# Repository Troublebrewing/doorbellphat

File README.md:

# doorbellphat
AC-DC psu bonnet/phat for pi zero. To be used with doorbell 12-24VAC.

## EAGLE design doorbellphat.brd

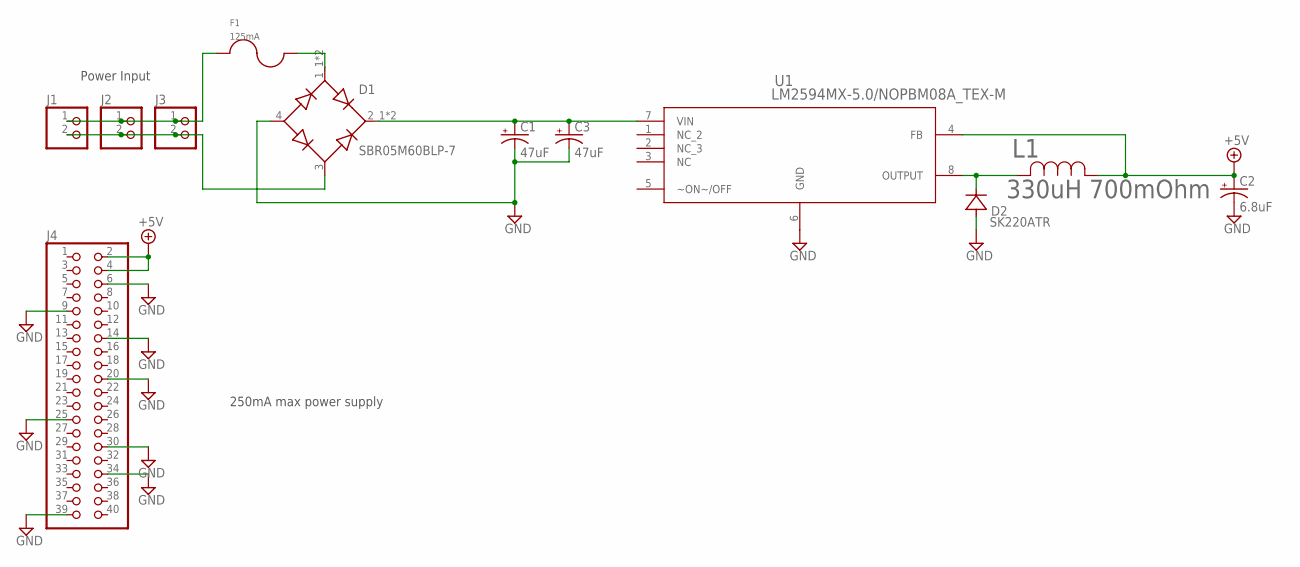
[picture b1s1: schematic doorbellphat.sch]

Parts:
C1, C3: 47uF; CAPPM7343X310N; MFR_PART_NO TAJD476M035RNJV
C2: 6.8uF; 2312; MFR_PART_NO 293D685X9035C2TE3
D1: SBR05M60BLP-7; RECTIFIER_SBR05M60BLP-7
D2: SK220ATR; SMA
F1: 125mA; 0603
J1, J2, J3: PINHD-1X2; 1X02
J4: PINHD-2X20; 2X20
L1: 330uH 700mOhm; IND_BOURNS_SRU1038; MFR_PART_NO SRU1038-331Y
U1: LM2594MX-5.0/NOPBM08A_TEX-M; M08A_TEX-M

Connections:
+5V: C2.A (+), J4.2, J4.4, L1.1, U1.4 (FB)
GND: C1.C (-), C2.C (-), C3.C (-), D1.4 (-), D2.A, J4.6, J4.9, J4.14, J4.20, J4.25, J4.30, J4.34, J4.39, U1.6 (GND)
unnamed: D1.3 (AC2), J1.2, J2.2, J3.2
unnamed: F1.1 (2), J1.1, J2.1, J3.1
unnamed: D2.C, L1.2, U1.8 (OUTPUT)
unnamed: D1.1_1 (AC1), D1.1_2 (AC1), F1.2 (1)
unnamed: C1.A (+), C3.A (+), D1.2_1 (+), D1.2_2 (+), U1.7 (VIN)

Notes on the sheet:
250mA max power supply
Power Input

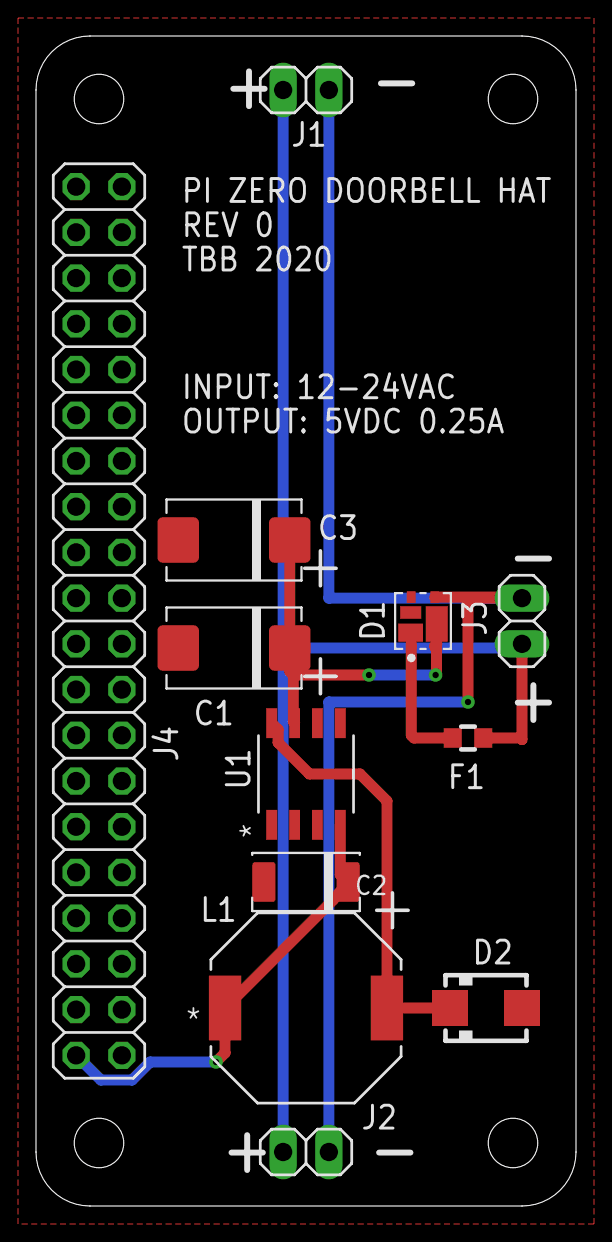
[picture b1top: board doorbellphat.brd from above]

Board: 2 copper layers, 30.0 x 65.0 mm, 12 parts (0 on the bottom side), 7 nets.

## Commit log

2020-07-06 schematic complete. layout complete. capacitor footprints might need to change. this board has no means to actuate physical doorbell chime
2020-07-06 first spin
2020-07-06 added pn to capacitors and polarity to rear silkscreen
2020-07-06 gerbers for first spin updated
